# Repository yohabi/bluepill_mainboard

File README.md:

# bluepill_mainboard

```
Blue Pill STM32F103C8T6
X2, X3  (screw terminal) for XL4015 DC/DC power supply discrete board,
1602 LCD
JP1 (dupont terminal): 10 input/output (PB3..PB7, PA9..PA15)
JP2 (dupont terminal): serial interface RX/TX (PB10..PB11)
JP3 (dupont terminal): 1 input/output (PB0)
JP4 (dupont terminal): 2 input/output (PB8..PB9)
JP9 (dupont terminal): battery power supply
Adjustment potentiometer at PA0..PA3
4 buttons at PA4..PA7
3 NPN switches at PB12..PB14
2 LEDs at PA8, PB15
```

Schematic:

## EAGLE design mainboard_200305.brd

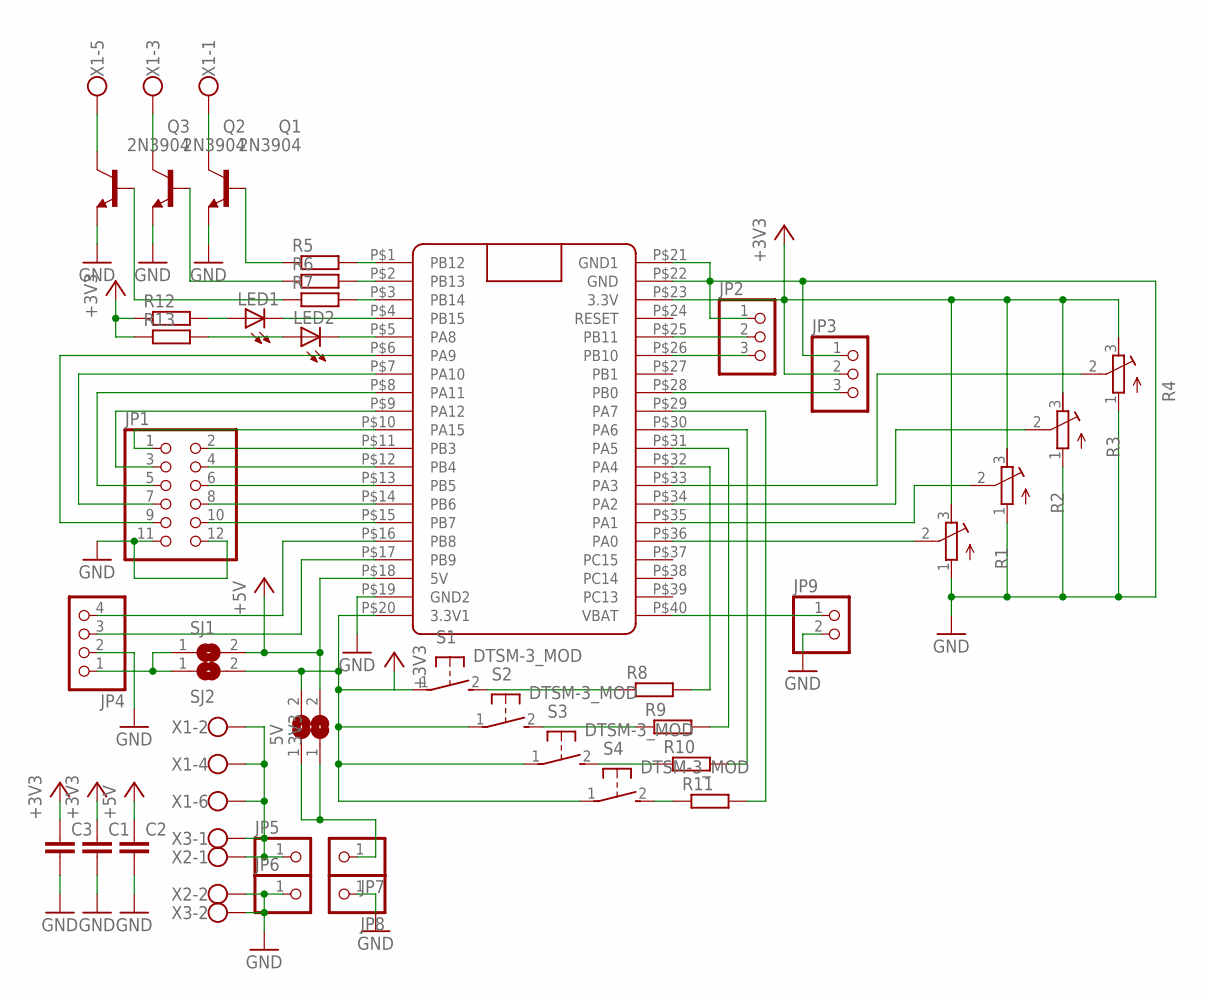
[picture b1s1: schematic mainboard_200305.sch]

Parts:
3V3, 5V: SJ
C1, C2, C3: C-EU050-045X075; C050-045X075
JP1: PINHD-2X6; 2X06
JP2, JP3: PINHD-1X3; 1X03
JP4: PINHD-1X4; 1X04
JP5, JP6, JP7, JP8: PINHD-1X1; 1X01
JP9: PINHD-1X2; 1X02
LED1, LED2: LEDCHIPLED_1206; CHIPLED_1206
Q1, Q2, Q3: 2N3904; TO92
R1, R2, R3, R4: R-TRIMM64W; RTRIM64W
R5, R6, R7, R8, R9, R10, R11, R12, R13: R-EU_R1206; R1206
S1, S2, S3, S4: DTSM-3_MOD
SJ1, SJ2: SJ
U$1: BLUE_PILL
X1: W237-6
X2, X3: W237-102

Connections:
+3V3: 5V.2, C1.1, C3.1, JP3.2, R1.3 (E), R2.3 (E), R3.3 (E), R4.3 (E), R12.1, R13.1, S1.1, S2.1, S3.1, S4.1, SJ2.2, U$1.P$20 (3.3V1), U$1.P$23 (3.3V)
+5V: 3V3.2, C2.1, SJ1.2, U$1.P$18 (5V)
GND: C1.2, C2.2, C3.2, JP1.11, JP1.12, JP2.1, JP3.1, JP4.2, JP6.1, JP8.1, JP9.2, Q1.3 (E), Q2.3 (E), Q3.3 (E), R1.1 (A), R2.1 (A), R3.1 (A), R4.1 (A), U$1.P$19 (GND2), U$1.P$21 (GND1), U$1.P$22 (GND), X2.2, X3.2
unnamed: R1.2 (S), U$1.P$36 (PA0)
unnamed: R2.2 (S), U$1.P$35 (PA1)
unnamed: R3.2 (S), U$1.P$34 (PA2)
unnamed: R4.2 (S), U$1.P$33 (PA3)
unnamed: JP1.2, U$1.P$11 (PB3)
unnamed: JP1.4, U$1.P$12 (PB4)
unnamed: JP1.6, U$1.P$13 (PB5)
unnamed: Q3.1 (C), X1.5
unnamed: JP4.1, SJ1.1, SJ2.1
unnamed: JP1.8, U$1.P$14 (PB6)
unnamed: JP1.10, U$1.P$15 (PB7)
unnamed: JP5.1, X1.2, X1.4, X1.6, X2.1, X3.1
unnamed: JP1.1, U$1.P$10 (PA15)
unnamed: Q2.2 (B), R6.1
unnamed: Q3.2 (B), R7.1
unnamed: Q1.2 (B), R5.1
unnamed: R5.2, U$1.P$1 (PB12)
unnamed: JP2.3, U$1.P$26 (PB10)
unnamed: JP2.2, U$1.P$25 (PB11)
unnamed: Q2.1 (C), X1.3
unnamed: JP3.3, U$1.P$28 (PB0)
unnamed: JP4.4, U$1.P$16 (PB8)
unnamed: JP4.3, U$1.P$17 (PB9)
unnamed: JP1.3, U$1.P$9 (PA12)
unnamed: JP1.5, U$1.P$8 (PA11)
unnamed: JP1.7, U$1.P$7 (PA10)
unnamed: JP1.9, U$1.P$6 (PA9)
unnamed: R6.2, U$1.P$2 (PB13)
unnamed: R7.2, U$1.P$3 (PB14)
unnamed: R11.1, S4.2
unnamed: R8.1, S1.2
unnamed: R10.1, S3.2
unnamed: R9.1, S2.2
unnamed: R8.2, U$1.P$32 (PA4)
unnamed: R9.2, U$1.P$31 (PA5)
unnamed: R10.2, U$1.P$30 (PA6)
unnamed: R11.2, U$1.P$29 (PA7)
unnamed: Q1.1 (C), X1.1
unnamed: LED2.A, R13.2
unnamed: LED2.C, U$1.P$5 (PA8)
unnamed: LED1.C, U$1.P$4 (PB15)
unnamed: LED1.A, R12.2
unnamed: JP9.1, U$1.P$40 (VBAT)
unnamed: 3V3.1, 5V.1, JP7.1

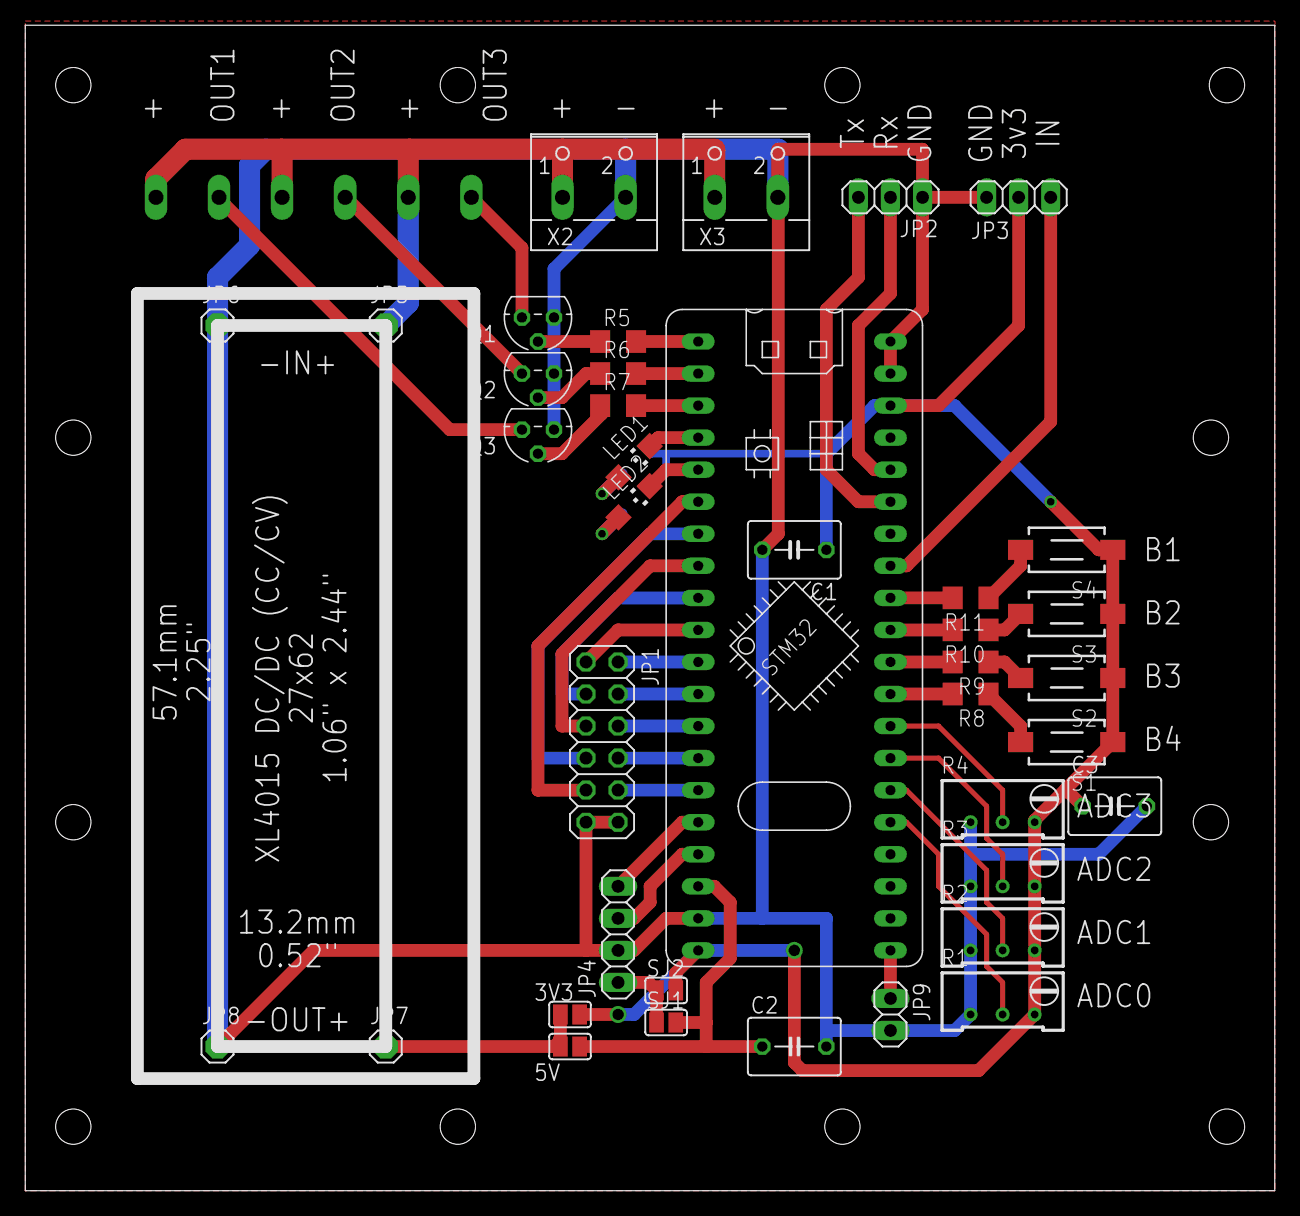
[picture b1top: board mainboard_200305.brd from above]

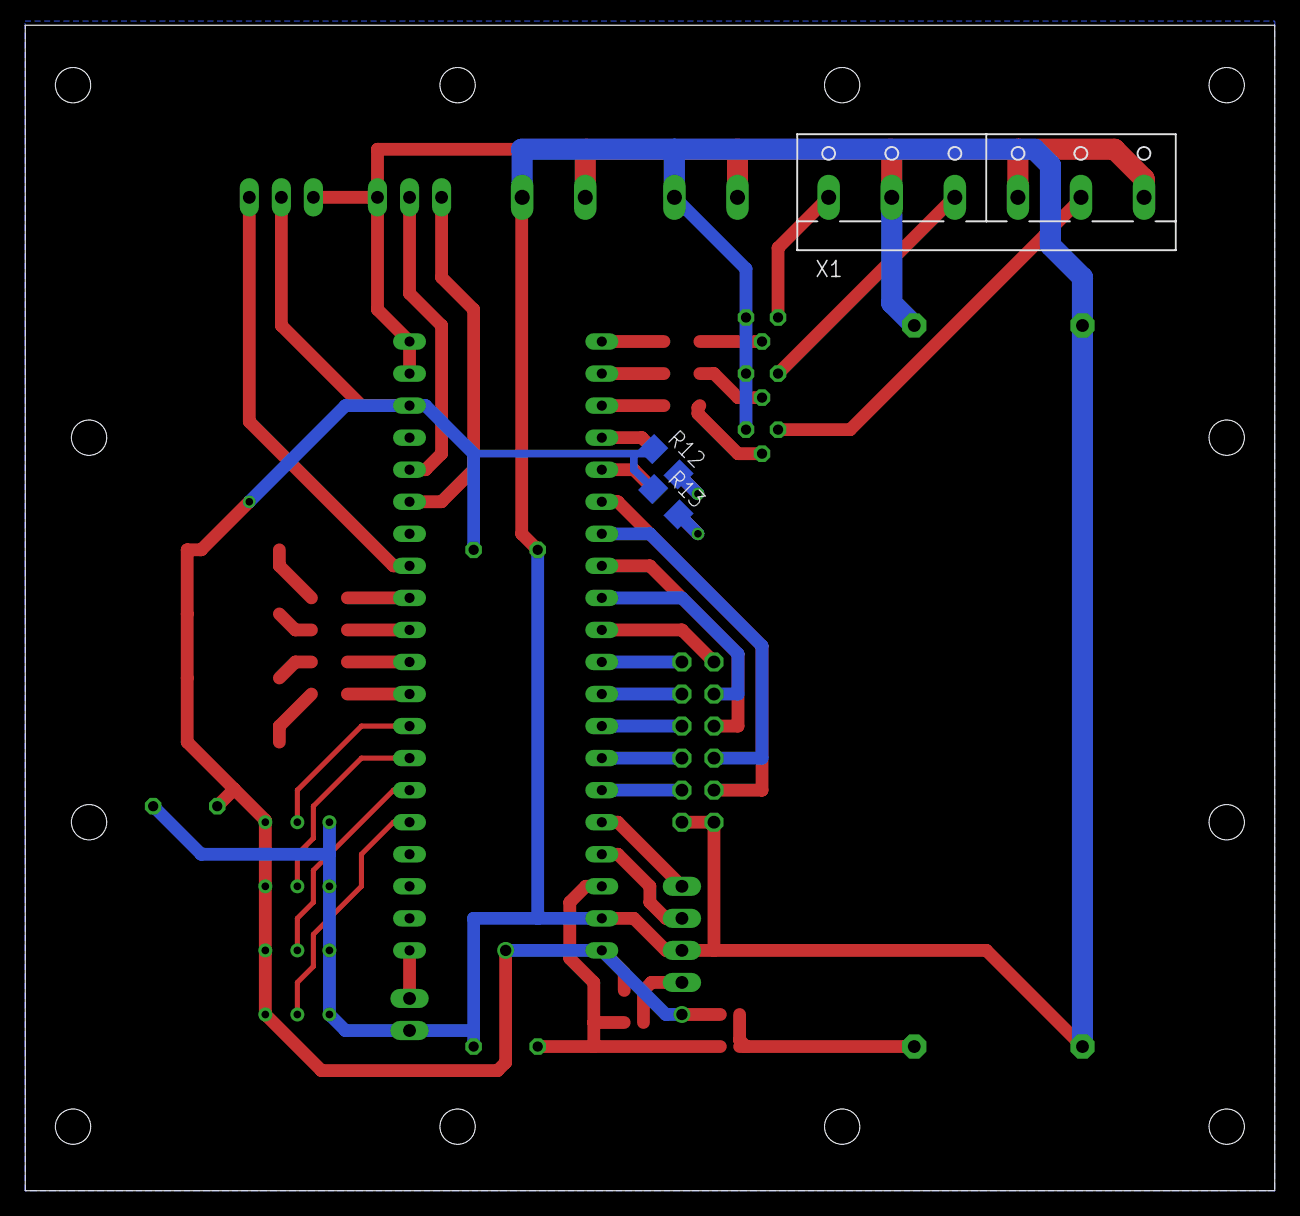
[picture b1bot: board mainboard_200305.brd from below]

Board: 2 copper layers, 99.0 x 92.4 mm, 42 parts (3 on the bottom side), 47 nets.
